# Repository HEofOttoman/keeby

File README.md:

<!-- # Kai-Board v1
Custom 65% compact keyboard made by I, Henry Wauzivuff. -->
<header align="center">
<h1>Kai-Board v1</h1>

<h4>Custom wireless 65% compact keyboard made by Henry Wauzivuff.</h4>
</header>

## Features
- Wireless potential + Rechargable battery slot
- 65% compact
- Joystick (my replacement of the Thinkpad trackball)
- 1x EC11 Rotary Encoder

In a future design, I hope to include a usb hub, on/off switches, LEDs & whatever makes better use of the IO expander I ended up using

## Images

### Schematic
(outdated)

### PCB

### CAD
Onshape link that may or may not [work](https://cad.onshape.com/documents/7e4f9e7530ad3774807d336c/w/6a2b4c794cd4ebe03f2424c9/e/2e40ded4774df0623cc9d47f?renderMode=0&uiState=6abe04a7d032dd1321beeb5d)

## BOM
|Qty|Item|Description|Cost (AUD/USD)|Link
|---|---|---|---|---|
|67x|MX Switches|Keys|||
|67x|1N4148|Diodes|||
|1x|Keycap Set|||
|1x|PCB||$$|
|1x|Case|housing duh|$|
|1x|PSP1000|Joystick maybe||
|2x|2.25u MX Stabilisers|||
|1x|6.25u MX Stabiliser|Spacebar|
|1x|2u MX Stabiliser|Backspace|
|1x|301230|Lipo Battery 500mAh|$2 (possible scam)|[aliexpress](https://www.aliexpress.com/item/32732458079.html?spm=a2g0o.productlist.main.5.518b1f629krtwf&algo_pvid=4e4df2b8-b7de-4edf-a95e-5e57bb996f07&algo_exp_id=4e4df2b8-b7de-4edf-a95e-5e57bb996f07-4&pdp_ext_f=%7B%22order%22%3A%22182%22%2C%22eval%22%3A%221%22%2C%22fromPage%22%3A%22search%22%7D&pdp_npi=6%40dis%21AUD%212.00%212.00%21%21%219.26%219.26%21%400b88ad2b17906635724894304e1329%2161434244877%21sea%21AU%210%21ABX%211%210%21n_tag%3A-29910%3Bd%3Aaa1881c%3Bm03_new_user%3A-29895&curPageLogUid=VuQ5vmTiasBg&utparam-url=scene%3Asearch%7Cquery_from%3A%7Cx_object_id%3A32732458079%7C_p_origin_prod%3A)|
|1x|MCP23017-SP GPIO Expanders||||

## References
Useful Links
- https://github.com/joric/nrfmicro/wiki
- https://github.com/RafaelCasamaximo/voidPointer
- https://github.com/ebastler/marbastlib (plugin & content manager)
- https://github.com/joric/nrfmicro/wiki/Pinout - Pinout, might be useful idk
- https://github.com/joric/nrfmicro/wiki/Alternatives/

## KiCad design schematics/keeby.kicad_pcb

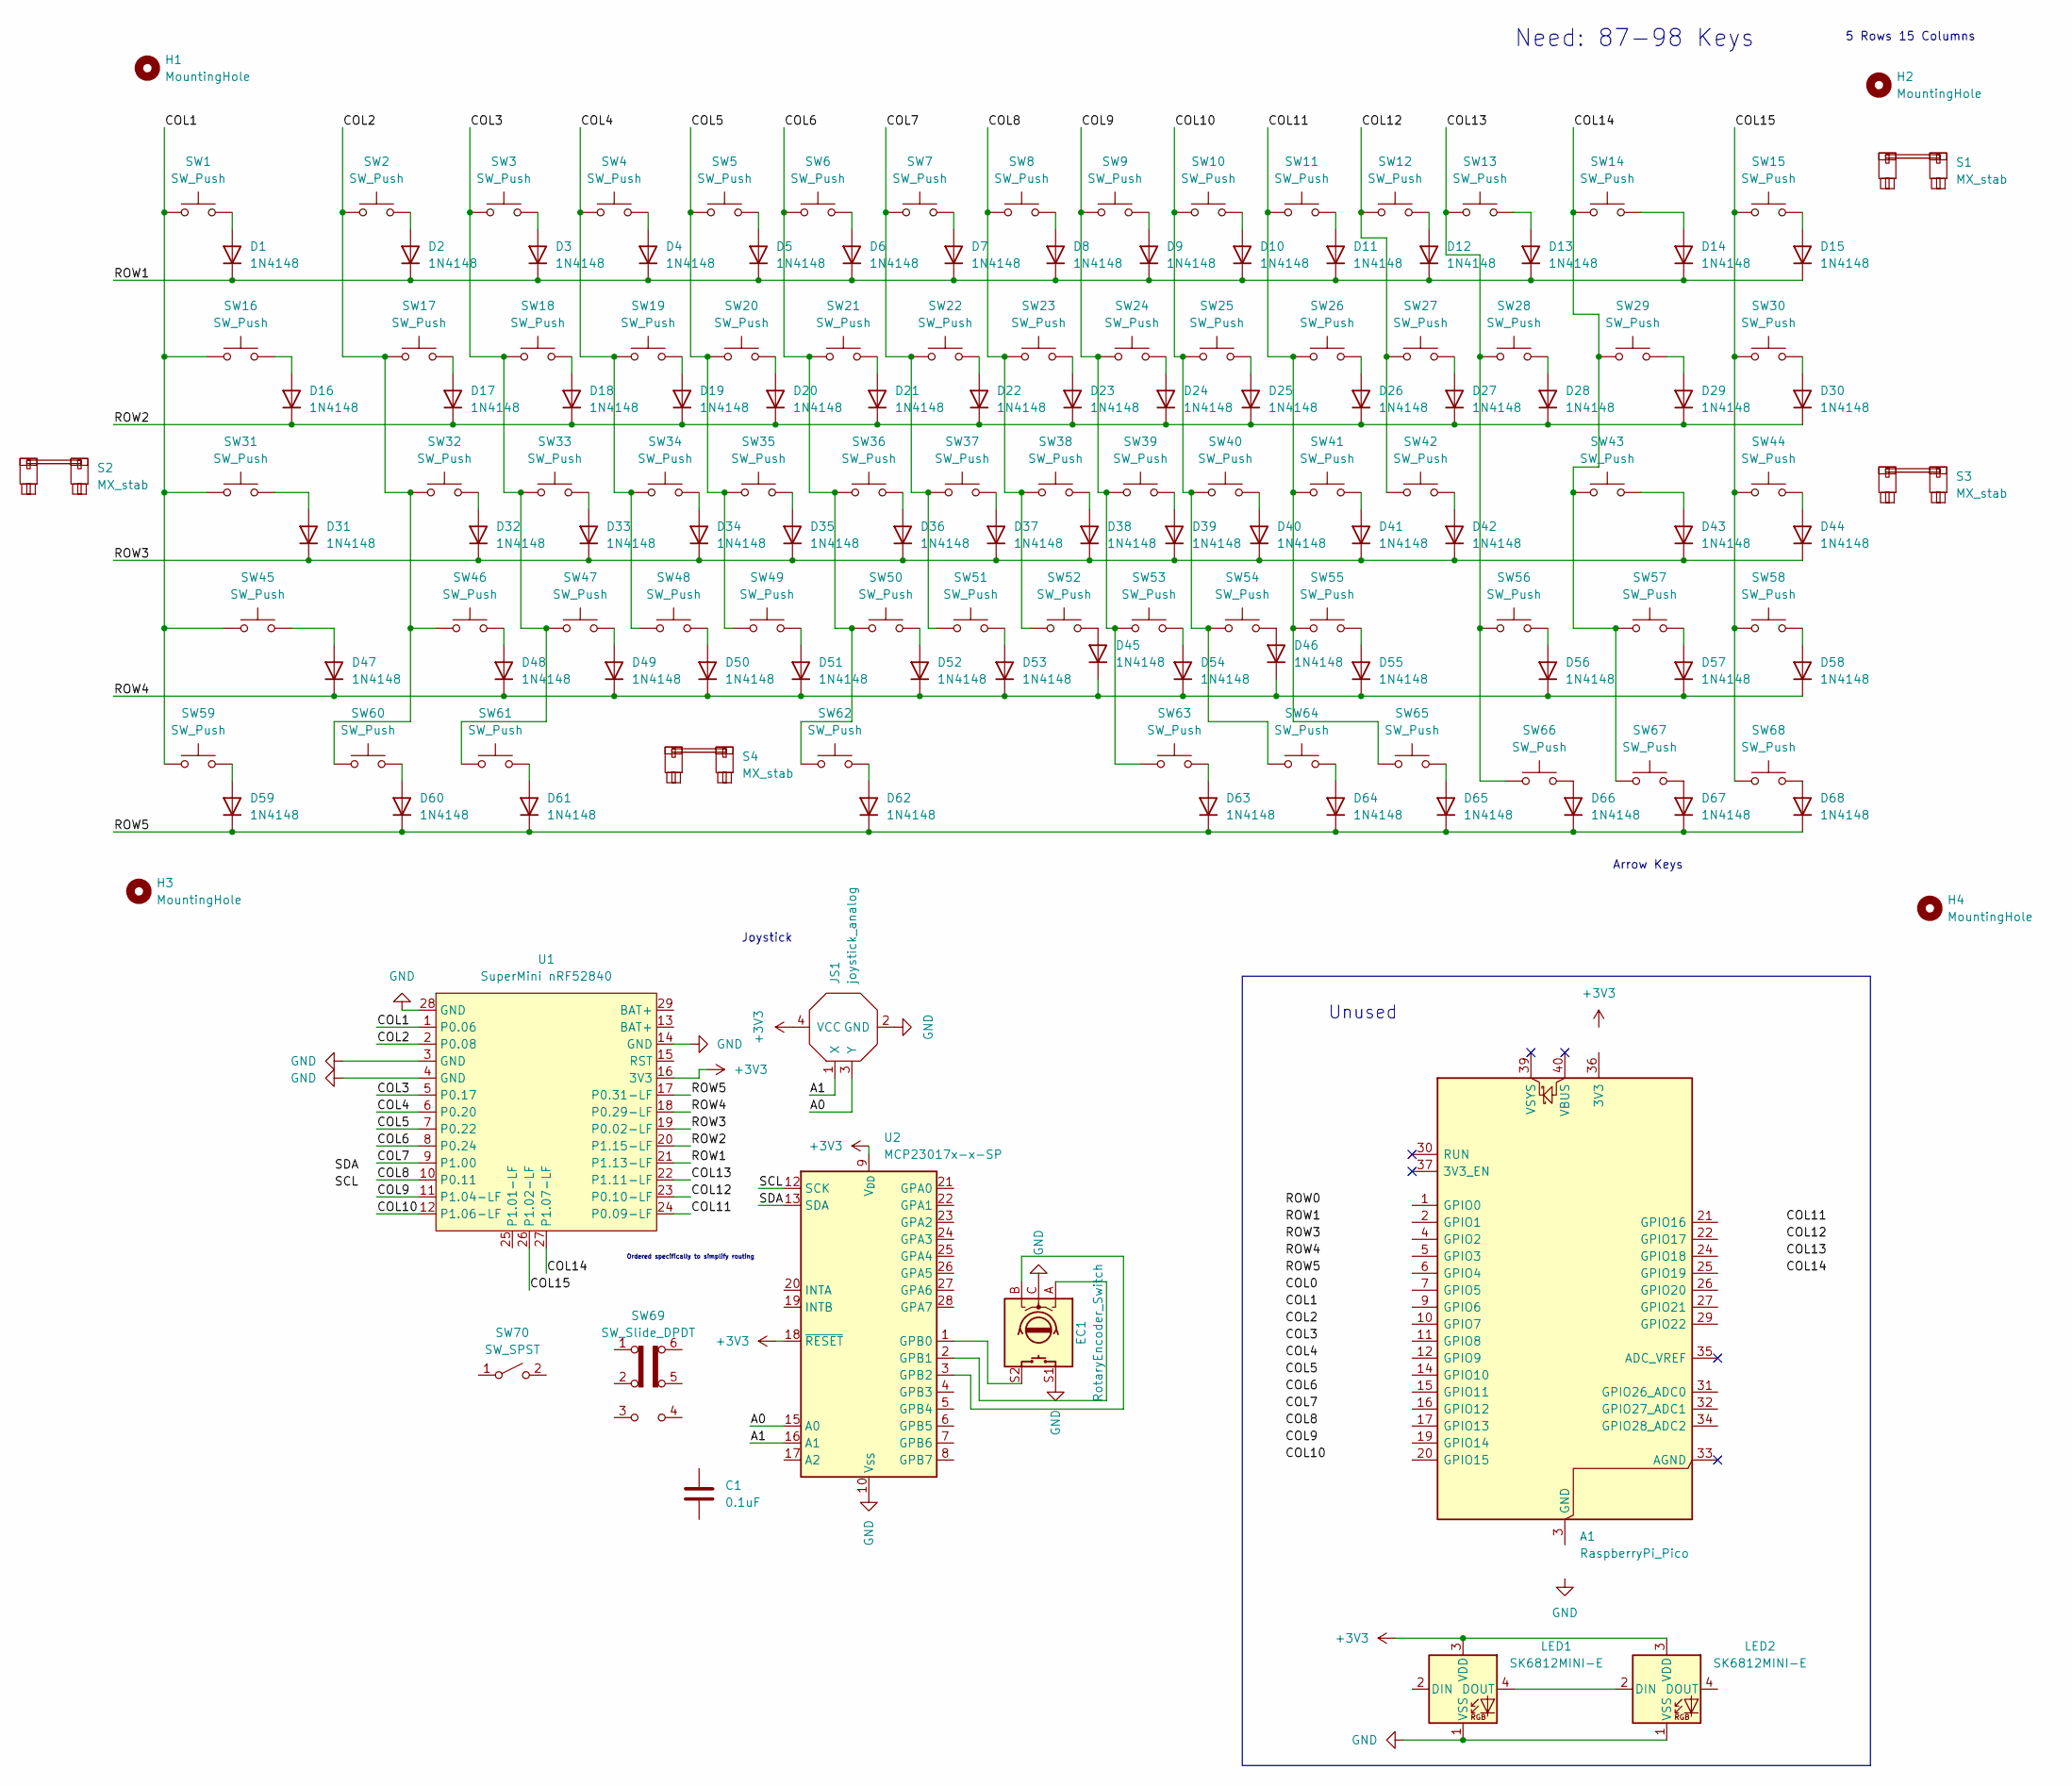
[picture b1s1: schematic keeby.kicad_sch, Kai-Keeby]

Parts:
A1: RaspberryPi_Pico; RaspberryPi_Pico_Common_THT
C1: 0.1uF
D1, D2, D3, D4, D5, D6, D7, D8, D9, D10, D11, D12, D13, D14, D15, D16, D17, D18, D19, D20, D21, D22, D23, D24, D25, D26, D27, D28, D29, D30, D31, D32, D33, D34, D35, D36, D37, D38, D39, D40, D41, D42, D43, D44, D45, D46, D47, D48, D49, D50, D51, D52, D53, D54, D55, D56, D57, D58, D59, D60, D61, D62, D63, D64, D65, D66, D67, D68: 1N4148; D_DO-35_SOD27_P7.62mm_Horizontal
EC1: RotaryEncoder_Switch; ROT_Alps_EC11E-Switch
H1, H2, H3, H4: MountingHole; MountingHole_2.2mm_M2
JS1: joystick_analog; PNT_psp1000
LED1, LED2: SK6812MINI-E; LED_SK6812MINI-E_3.2x2.8mm_P1.5mm_ReverseMount
S1, S3: MX_stab; STAB_MX_2.25u
S2: MX_stab; STAB_MX_2u
S4: MX_stab; STAB_MX_6.25u
SW1, SW2, SW3, SW4, SW5, SW6, SW7, SW8, SW9, SW10, SW11, SW12, SW13, SW14, SW15, SW16, SW17, SW18, SW19, SW20, SW21, SW22, SW23, SW24, SW25, SW26, SW27, SW28, SW29, SW30, SW31, SW32, SW33, SW34, SW35, SW36, SW37, SW38, SW39, SW40, SW41, SW42, SW43, SW44, SW45, SW46, SW47, SW48, SW49, SW50, SW51, SW52, SW53, SW54, SW55, SW56, SW57, SW58, SW59, SW60, SW61, SW62, SW63, SW64, SW65, SW66, SW67, SW68: SW_Push; SW_MX_1u
SW69: SW_Slide_DPDT
SW70: SW_SPST
U1: SuperMini nRF52840; SuperMini_nRF52840_AH_USBup
U2: MCP23017x-x-SP; DIP-28_W7.62mm

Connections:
+3V3: JS1.4 (VCC), LED1.3 (VDD), LED2.3 (VDD), U1.16 (3V3), U2.9 (V_{DD}), U2.18 (~RESET)
/A0: JS1.3 (Y), U2.15 (A0)
/A1: JS1.1 (X), U2.16 (A1)
/COL1: SW1.1, SW16.1, SW31.1, SW45.1, SW59.1, U1.1 (P0.06)
/COL2: SW2.1, SW17.1, SW32.1, SW46.1, SW60.1, U1.2 (P0.08)
/COL3: SW3.1, SW18.1, SW33.1, SW47.1, SW61.1, U1.5 (P0.17)
/COL4: SW4.1, SW19.1, SW34.1, SW48.1, U1.6 (P0.20)
/COL5: SW5.1, SW20.1, SW35.1, SW49.1, U1.7 (P0.22)
/COL6: SW6.1, SW21.1, SW36.1, SW50.1, SW62.1, U1.8 (P0.24)
/COL7: SW7.1, SW22.1, SW37.1, SW51.1, U1.9 (P1.00)
/COL8: SW8.1, SW23.1, SW38.1, SW52.1, U1.10 (P0.11)
/COL9: SW9.1, SW24.1, SW39.1, SW53.1, SW63.1, U1.11 (P1.04-LF)
/COL10: SW10.1, SW25.1, SW40.1, SW54.1, SW64.1, U1.12 (P1.06-LF)
/COL11: SW11.1, SW26.1, SW41.1, SW55.1, SW65.1, U1.24 (P0.09-LF)
/COL12: SW12.1, SW27.1, SW42.1, U1.23 (P0.10-LF)
/COL13: SW13.1, SW28.1, SW56.1, SW66.1, U1.22 (P1.11-LF)
/COL14: SW14.1, SW29.1, SW43.1, SW57.1, SW67.1, U1.27 (P1.07-LF)
/COL15: SW15.1, SW30.1, SW44.1, SW58.1, SW68.1, U1.26 (P1.02-LF)
/ROW1: D1.1 (K), D2.1 (K), D3.1 (K), D4.1 (K), D5.1 (K), D6.1 (K), D7.1 (K), D8.1 (K), D9.1 (K), D10.1 (K), D11.1 (K), D12.1 (K), D13.1 (K), D14.1 (K), D15.1 (K), U1.21 (P1.13-LF)
/ROW2: D16.1 (K), D17.1 (K), D18.1 (K), D19.1 (K), D20.1 (K), D21.1 (K), D22.1 (K), D23.1 (K), D24.1 (K), D25.1 (K), D26.1 (K), D27.1 (K), D28.1 (K), D29.1 (K), D30.1 (K), U1.20 (P1.15-LF)
/ROW3: D31.1 (K), D32.1 (K), D33.1 (K), D34.1 (K), D35.1 (K), D36.1 (K), D37.1 (K), D38.1 (K), D39.1 (K), D40.1 (K), D41.1 (K), D42.1 (K), D43.1 (K), D44.1 (K), U1.19 (P0.02-LF)
/ROW4: D45.1 (K), D46.1 (K), D47.1 (K), D48.1 (K), D49.1 (K), D50.1 (K), D51.1 (K), D52.1 (K), D53.1 (K), D54.1 (K), D55.1 (K), D56.1 (K), D57.1 (K), D58.1 (K), U1.18 (P0.29-LF)
/ROW5: D59.1 (K), D60.1 (K), D61.1 (K), D62.1 (K), D63.1 (K), D64.1 (K), D65.1 (K), D66.1 (K), D67.1 (K), D68.1 (K), U1.17 (P0.31-LF)
/SCL: U2.12 (SCK)
/SDA: U2.13 (SDA)
GND: EC1.C, EC1.S1, JS1.2 (GND), LED1.1 (VSS), LED2.1 (VSS), U1.3 (GND), U1.4 (GND), U1.14 (GND), U1.28 (GND), U2.10 (V_{SS})
unnamed: A1.3 (GND), A1.8 (GND), A1.13 (GND), A1.18 (GND), A1.23 (GND), A1.28 (GND), A1.38 (GND)
unnamed: D1.2 (A), SW1.2
unnamed: D2.2 (A), SW2.2
unnamed: D3.2 (A), SW3.2
unnamed: D4.2 (A), SW4.2
unnamed: D5.2 (A), SW5.2
unnamed: D6.2 (A), SW6.2
unnamed: D7.2 (A), SW7.2
unnamed: D8.2 (A), SW8.2
unnamed: D9.2 (A), SW9.2
unnamed: D10.2 (A), SW10.2
unnamed: D11.2 (A), SW11.2
unnamed: D12.2 (A), SW12.2
unnamed: D13.2 (A), SW13.2
unnamed: D14.2 (A), SW14.2
unnamed: D15.2 (A), SW15.2
unnamed: D16.2 (A), SW16.2
unnamed: D17.2 (A), SW17.2
unnamed: D18.2 (A), SW18.2
unnamed: D19.2 (A), SW19.2
unnamed: D20.2 (A), SW20.2
unnamed: D21.2 (A), SW21.2
unnamed: D22.2 (A), SW22.2
unnamed: D23.2 (A), SW23.2
unnamed: D24.2 (A), SW24.2
unnamed: D25.2 (A), SW25.2
unnamed: D26.2 (A), SW26.2
unnamed: D27.2 (A), SW27.2
unnamed: D28.2 (A), SW28.2
unnamed: D29.2 (A), SW29.2
unnamed: D30.2 (A), SW30.2
unnamed: D31.2 (A), SW31.2
unnamed: D32.2 (A), SW32.2
unnamed: D33.2 (A), SW33.2
unnamed: D34.2 (A), SW34.2
unnamed: D35.2 (A), SW35.2
unnamed: D36.2 (A), SW36.2
unnamed: D37.2 (A), SW37.2
unnamed: D38.2 (A), SW38.2
unnamed: D39.2 (A), SW39.2
unnamed: D40.2 (A), SW40.2
unnamed: D41.2 (A), SW41.2
unnamed: D42.2 (A), SW42.2
unnamed: D43.2 (A), SW43.2
unnamed: D44.2 (A), SW44.2
unnamed: D45.2 (A), SW52.2
unnamed: D46.2 (A), SW54.2
unnamed: D47.2 (A), SW45.2
unnamed: D48.2 (A), SW46.2
unnamed: D49.2 (A), SW47.2
unnamed: D50.2 (A), SW48.2
unnamed: D51.2 (A), SW49.2
unnamed: D52.2 (A), SW50.2
unnamed: D53.2 (A), SW51.2
unnamed: D54.2 (A), SW53.2
unnamed: D55.2 (A), SW55.2
unnamed: D56.2 (A), SW56.2
unnamed: D57.2 (A), SW57.2
unnamed: D58.2 (A), SW58.2
unnamed: D59.2 (A), SW59.2
unnamed: D60.2 (A), SW60.2
unnamed: D61.2 (A), SW61.2
unnamed: D62.2 (A), SW62.2
unnamed: D63.2 (A), SW63.2
unnamed: D64.2 (A), SW64.2
unnamed: D65.2 (A), SW65.2
unnamed: D66.2 (A), SW66.2
unnamed: D67.2 (A), SW67.2
unnamed: D68.2 (A), SW68.2
unnamed: LED1.4 (DOUT), LED2.2 (DIN)
unnamed: EC1.S2, U2.1 (GPB0)
unnamed: EC1.A, U2.2 (GPB1)
unnamed: EC1.B, U2.3 (GPB2)

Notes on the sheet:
Ordered specifically to simplify routing
Arrow Keys
Joystick
Need: 87-98 Keys
Unused
5 Rows 15 Columns

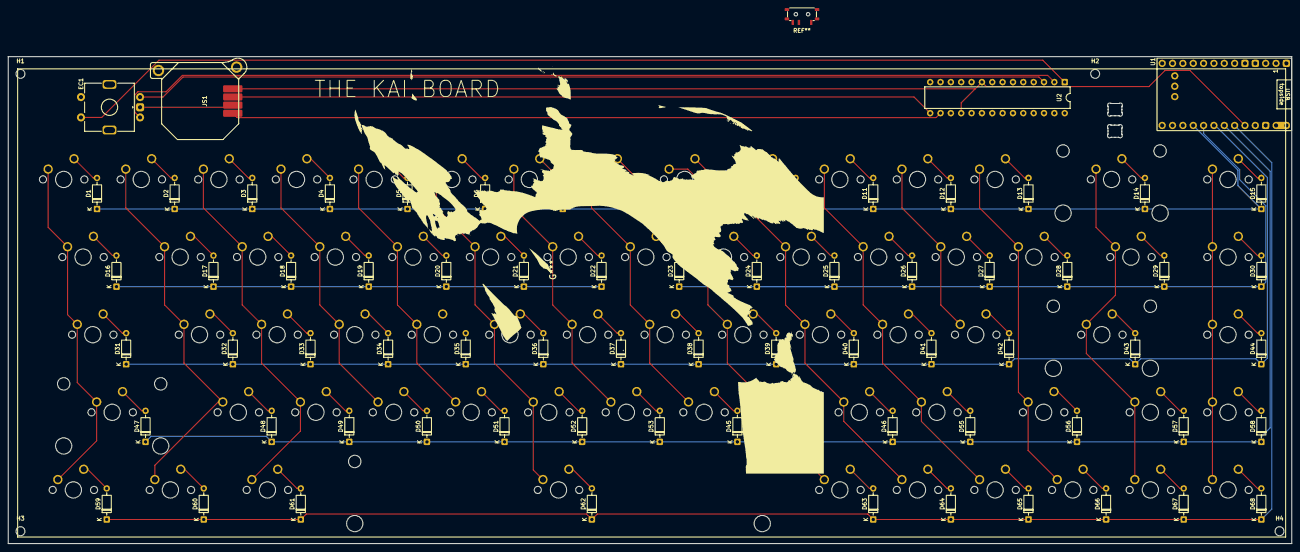
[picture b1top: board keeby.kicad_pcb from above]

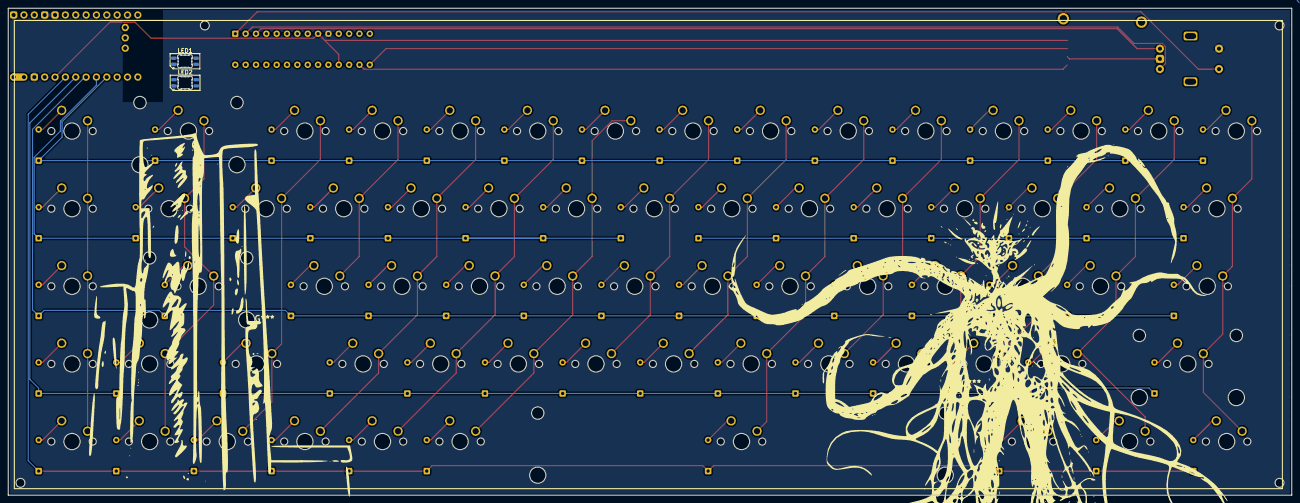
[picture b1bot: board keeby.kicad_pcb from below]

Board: 2 copper layers, 315.0 x 119.5 mm, 150 parts (2 on the bottom side), 96 nets.

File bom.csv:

"Id";"Designator";"Footprint";"Quantity";"Designation";"Supplier and ref";
1;"D1, D2, D3, D4, D5, D6, D7, D8, D9, D10, D11, D12, D13, D14, D15, D16, D17, D18, D19, D20, D21, D22, D23, D24, D25, D26, D27, D28, D29, D30, D31, D32, D33, D34, D35, D36, D37, D38, D39, D40, D41, D42, D43, D44, D45, D46, D47, D48, D49, D50, D51, D52, D53, D54, D55, D56, D57, D58, D59, D60, D61, D62, D63, D64, D65, D66, D67, D68";"D_DO-35_SOD27_P7.62mm_Horizontal";68;"1N4148";;;
2;"EC1";"ROT_Alps_EC11E-Switch";1;"RotaryEncoder_Switch";;;
3;"JS1";"PNT_psp1000";1;"joystick_analog";;;
4;"LED1, LED2";"LED_SK6812MINI-E_3.2x2.8mm_P1.5mm_ReverseMount";2;"SK6812MINI-E";;;
5;"REF**";"SW_MSK12C02-HB";1;"SW_MSK12C02-HB";;;
6;"S1, S3";"STAB_MX_2.25u";2;"MX_stab";;;
7;"S2";"STAB_MX_2u";1;"MX_stab";;;
8;"S4";"STAB_MX_6.25u";1;"MX_stab";;;
9;"SW1, SW2, SW3, SW4, SW5, SW6, SW7, SW8, SW9, SW10, SW11, SW12, SW13, SW14, SW15, SW16, SW17, SW18, SW19, SW20, SW21, SW22, SW23, SW24, SW25, SW26, SW27, SW28, SW29, SW30, SW31, SW32, SW33, SW34, SW35, SW36, SW37, SW38, SW39, SW40, SW41, SW42, SW43, SW44, SW45, SW46, SW47, SW48, SW49, SW50, SW51, SW52, SW53, SW54, SW55, SW56, SW57, SW58, SW59, SW60, SW61, SW62, SW63, SW64, SW65, SW66, SW67, SW68";"SW_MX_1u";68;"SW_Push";;;
10;"U2";"DIP-28_W7.62mm";1;"MCP23017x-x-SP";;;
